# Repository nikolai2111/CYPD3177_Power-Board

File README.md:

# CYPD3177_Power-Board <!-- omit from toc -->

## Content <!-- omit from toc -->
- [1. Description](#1-description)
- [2. Folder structure](#2-folder-structure)
- [3. Usage](#3-usage)
- [4. License](#4-license)

## 1. Description
TBC: Easy to use and programmable power board for powering your electronics with up to 100 watts of power.

## 2. Folder structure
TBC

## 3. Usage
Add instructions and examples here.

## 4. License
The hardware and its documentation is licensed under the CERN-OHL-P licence, which can be found [here](LICENSE).

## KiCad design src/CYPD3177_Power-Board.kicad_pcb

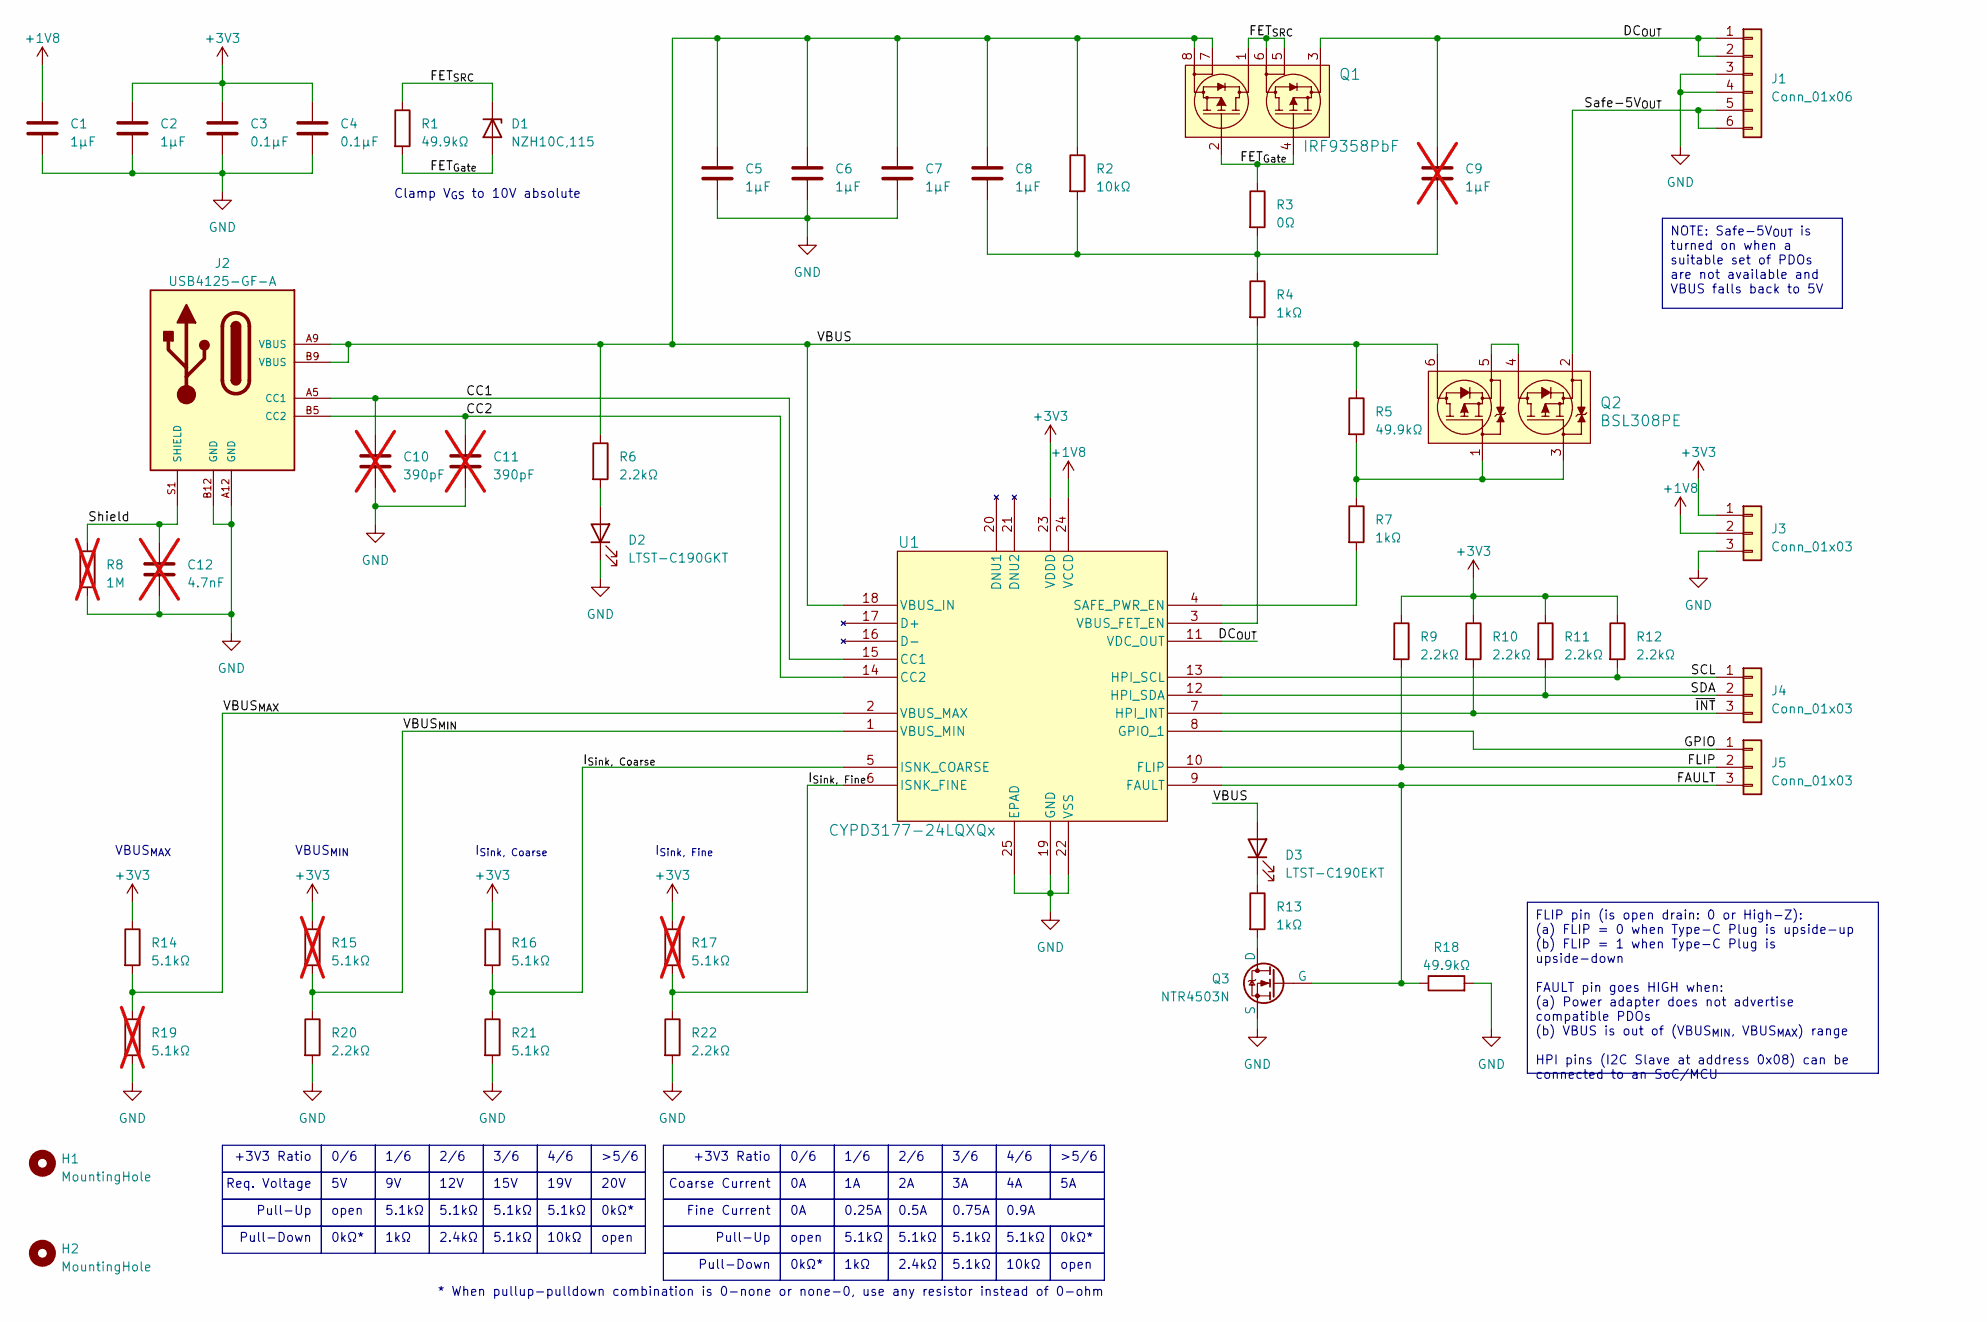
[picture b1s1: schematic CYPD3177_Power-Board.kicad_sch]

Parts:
C1, C2: 1µF; C_0603_1608Metric
C3, C4: 0.1µF; C_0402_1005Metric
C5, C6, C7, C8: 1µF; C_0402_1005Metric
C9: 1µF; C_0402_1005Metric_Pad0.74x0.62mm_HandSolder; not fitted
C10, C11: 390pF; C_0603_1608Metric_Pad1.08x0.95mm_HandSolder; not fitted
C12: 4.7nF; C_0603_1608Metric_Pad1.08x0.95mm_HandSolder; not fitted
D1: NZH10C,115; D_SOD-123F
D2: LTST-C190GKT; LED_0603_1608Metric_Pad1.05x0.95mm_HandSolder
D3: LTST-C190EKT; LED_0603_1608Metric_Pad1.05x0.95mm_HandSolder
H1, H2: MountingHole; MountingHole_3.2mm_M3
J1: Conn_01x06; CastellatedHole_1x06_P2.54mm_PinHeaders
J2: USB4125-GF-A; GCT_USB4125-GF-A
J3, J4, J5: Conn_01x03; CastellatedHole_1x03_P2.54mm_PinHeader
Q1: IRF9358PbF; HSOP-8-1EP_3.9x4.9mm_P1.27mm_EP2.41x3.1mm_ThermalVias
Q2: BSL308PE; SOT-23-6
Q3: NTR4503N; SOT-23-3
R1, R5: 49.9kΩ; R_0402_1005Metric
R2: 10kΩ; R_0603_1608Metric
R3: 0Ω; R_0402_1005Metric_Pad0.72x0.64mm_HandSolder
R4, R7: 1kΩ; R_0402_1005Metric
R6, R9, R10, R11, R12, R20, R22: 2.2kΩ; R_0805_2012Metric_Pad1.20x1.40mm_HandSolder
R8: 1M; R_0603_1608Metric_Pad0.98x0.95mm_HandSolder; not fitted
R13: 1kΩ; R_0402_1005Metric_Pad0.72x0.64mm_HandSolder
R14, R16, R21: 5.1kΩ; R_0805_2012Metric_Pad1.20x1.40mm_HandSolder
R15, R17, R19: 5.1kΩ; R_0805_2012Metric_Pad1.20x1.40mm_HandSolder; not fitted
R18: 49.9kΩ; R_0402_1005Metric_Pad0.72x0.64mm_HandSolder
U1: CYPD3177-24LQXQx; QFN-24-1EP_4x4mm_P0.5mm_EP2.7x2.7mm_ThermalVias

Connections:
+1V8: C1.1, J3.2, U1.24 (VCCD)
+3V3: C2.1, C3.1, C4.1, J3.1, R9.1, R10.1, R11.1, R12.1, R14.1, R15.1, R16.1, R17.1, U1.23 (VDDD)
/CC1: C10.1, J2.A5 (CC1), U1.15 (CC1)
/CC2: C11.1, J2.B5 (CC2), U1.14 (CC2)
/DC_{OUT}: C9.1, J1.1, J1.2, Q1.3, U1.11 (VDC_OUT)
/FAULT: J5.3, Q3.2 (G), R18.1, U1.9 (FAULT)
/FET_{Gate}: D1.2 (A), Q1.2, Q1.4, R1.2, R3.1
/FET_{SRC}: D1.1 (K), Q1.1, Q1.5, Q1.6, R1.1
/FLIP: J5.2, R9.2, U1.10 (FLIP)
/GPIO: J5.1, U1.8 (GPIO_1)
/I_{Sink, Coarse}: R16.2, R21.1, U1.5 (ISNK_COARSE)
/I_{Sink, Fine}: R17.2, R22.1, U1.6 (ISNK_FINE)
/SCL: J4.1, R12.2, U1.13 (HPI_SCL)
/SDA: J4.2, R11.2, U1.12 (HPI_SDA)
/Safe-5V_{OUT}: J1.5, J1.6, Q2.2
/Shield: C12.1, J2.S1 (SHIELD), R8.1
/VBUS: C5.1, C6.1, C7.1, C8.1, D3.2 (A), J2.A9 (VBUS), J2.B9 (VBUS), Q1.7, Q1.8, Q2.6, R2.1, R5.1, R6.1, U1.18 (VBUS_IN)
/VBUS_{MAX}: R14.2, R19.1, U1.2 (VBUS_MAX)
/VBUS_{MIN}: R15.2, R20.1, U1.1 (VBUS_MIN)
/~INT: J4.3, R10.2, U1.7 (HPI_INT)
GND: C1.2, C2.2, C3.2, C4.2, C5.2, C6.2, C7.2, C10.2, C11.2, C12.2, D2.1 (K), J1.3, J1.4, J2.A12 (GND), J2.B12 (GND), J3.3, Q1.9, Q3.3 (S), R8.2, R18.2, R19.2, R20.2, R21.2, R22.2, U1.19 (GND), U1.22 (VSS), U1.25 (EPAD)
unnamed: C8.2, C9.2, R2.2, R3.2, R4.1
unnamed: D2.2 (A), R6.2
unnamed: D3.1 (K), R13.1
unnamed: Q2.1, Q2.3, R5.2, R7.1
unnamed: Q2.4, Q2.5
unnamed: Q3.1 (D), R13.2
unnamed: R7.2, U1.4 (SAFE_PWR_EN)
unnamed: R4.2, U1.3 (VBUS_FET_EN)

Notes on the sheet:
FLIP pin (is open drain: 0 or High-Z): (a) FLIP = 0 when Type-C Plug is upside-up (b) FLIP = 1 when Type-C Plug is upside-down FAULT pin goes HIGH when: (a) Power adapter does not advertise compatible PDOs (b) VBUS is out of (VBUS_{MIN}, VBUS_{MAX}) range HPI pins (I2C Slave at address 0x08) can be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
NOTE: Safe-5V_{OUT} is turned on when a suitable set of PDOs are not available and VBUS falls back to 5V
5.1kΩ
Clamp V_{GS} to 10V absolute
1/6
Pull-Down
Pull-Up
0.9A
I_{Sink, Fine}
* When pullup-pulldown combination is 0-none or none-0, use any resistor instead of 0-ohm
1kΩ
10kΩ
+3V3 Ratio
2.4kΩ
VBUS_{MIN}
>5/6
4/6
Fine Current
0kΩ*
open
0.75A
3/6
19V
2/6
VBUS_{MAX}
0/6
0.25A
Req. Voltage
20V
I_{Sink, Coarse}
12V
Coarse Current
15V
0.5A

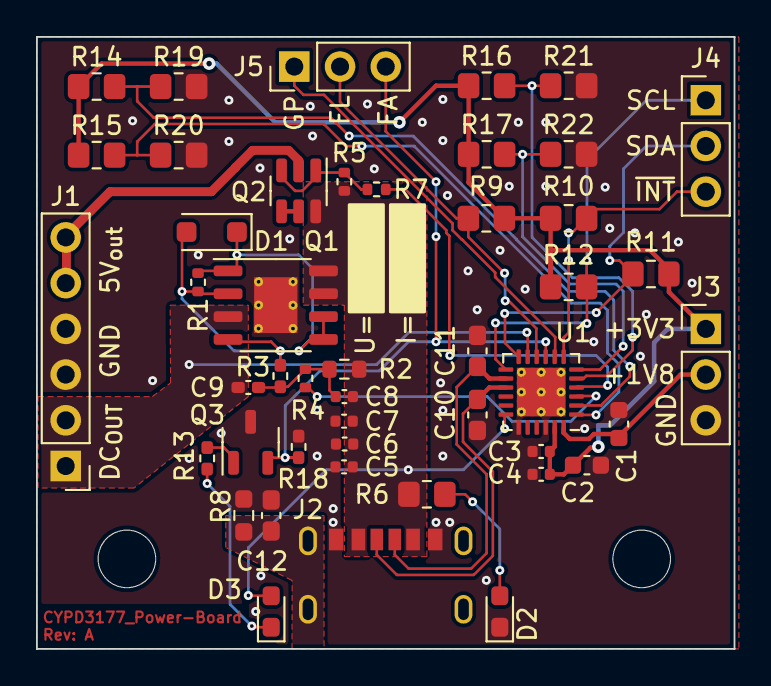
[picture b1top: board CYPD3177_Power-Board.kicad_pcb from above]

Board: 2 copper layers, 38.8 x 34.0 mm, 49 parts (0 on the bottom side), 29 nets.

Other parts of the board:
G0: LOGO; elektronik-emblem_3x3.5_solder

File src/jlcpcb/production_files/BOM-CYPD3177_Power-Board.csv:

Comment,Designator,Footprint,LCSC
1M,R8,R_0603_1608Metric_Pad0.98x0.95mm_HandSolder,C105578
4.7nF,C12,C_0603_1608Metric_Pad1.08x0.95mm_HandSolder,C106218
1kΩ,"R13,R4,R7",R_0402_1005Metric_Pad0.72x0.64mm_HandSolder,C106235
2.2kΩ,"R10,R11,R12,R20,R22,R6,R9",R_0805_2012Metric_Pad1.20x1.40mm_HandSolder,C114561
LTST-C190GKT,D2,LED_0603_1608Metric_Pad1.05x0.95mm_HandSolder,C125093
IRF9358PbF,Q1,HSOP-8-1EP_3.9x4.9mm_P1.27mm_EP2.41x3.1mm_ThermalVias,C150907
390pF,"C10,C11",C_0603_1608Metric_Pad1.08x0.95mm_HandSolder,C1617
10kΩ,R2,R_0603_1608Metric,C234237
CYPD3177-24LQXQx,U1,QFN-24-1EP_4x4mm_P0.5mm_EP2.7x2.7mm_ThermalVias,C2959321
1µF,"C5,C6,C7,C8,C9",C_0402_1005Metric,C307413
0.1µF,"C3,C4",C_0402_1005Metric,C309458
USB4125-GF-A,J2,GCT_USB4125-GF-A,C3151650
BSL308PE,Q2,SOT-23-6,C3289349
LTST-C190EKT,D3,LED_0603_1608Metric_Pad1.05x0.95mm_HandSolder,C364560
49.9kΩ,"R1,R18,R5",R_0402_1005Metric,C409918
NTR4503N,Q3,SOT-23-3,C5236683
"NZH10C,115",D1,D_SOD-123F,C551630
1µF,"C1,C2",C_0603_1608Metric,C59782
0Ω,R3,R_0402_1005Metric_Pad0.72x0.64mm_HandSolder,C60490
5.1kΩ,"R14,R15,R16,R17,R19,R21",R_0805_2012Metric_Pad1.20x1.40mm_HandSolder,C84375
Conn_01x06,J1,PinHeader_1x06_P2.54mm_Vertical,
Conn_01x03,J3,PinHeader_1x03_P2.54mm_Vertical,
Conn_01x03,J4,PinHeader_1x03_P2.54mm_Vertical,
Conn_01x03,J5,PinHeader_1x03_P2.54mm_Vertical,

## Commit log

2023-05-19 Mod: .gitignore, added some default files and modified the README to my default one
2023-05-19 Add: Default project from template
2023-05-19 Add: InfineonData for the CY4533, an evaluation platform with the CYPD3177
2023-05-19 Add: Initialized schematic, used the Infineon-CY4533_Guide-UserManual as a guide
2023-05-20 Mod: Schematic, modified some resistor value to not use as much; Add: Description texts and tables
2023-05-20 Mod: Power connector and changed date
2023-05-20 Mod: Assigned all footprints, without the connectors
2023-05-20 Add: Footprint for the connectors (castellated holes) and mounting holes
2023-05-23 Mod: Footpints and changes order of the power outputs on J1
2023-05-23 Mod: PCB, placed components, draw board shape and placed a few traces
2023-05-26 Del: Pictures, no longer needed
2023-05-26 Mod: Moved voltage dividers and placed all traces
2023-05-28 Mod: PCB, last touches, moved logo, added some more vias and some pin labels
2023-05-28 Add: Dimensions and moved holes and castellated holes
2023-05-28 Mod: PCB, removed all errors, for that the castellated holes, the USB connector and more had to be adjusted
2023-05-28 Add: Parts from LCSC
2023-05-28 Mod: JLCPCB database
2023-05-29 Mod: Corrected the pin alignment so that the possible pin header would be on the same 2.54mm grid
2023-05-29 Mod: Changed castellated holes to pin headers because they are cheapter
2023-05-29 Mod: Changed thermal pad of Q1 to the GND plane
2023-05-29 Add: LCSC part nr. to the scheme and added designator U1 to the PCB
2023-06-06 Mod: Exported some PDFs and picture, also added a README about he license for the folder InfineonData
2023-06-14 Dbug: Schematic, changed the connection between the two MOSFETs in both of the output FETs (Q1, Q2)
2023-06-20 Mod: Schematic and database, changed LCSC part number of R3
